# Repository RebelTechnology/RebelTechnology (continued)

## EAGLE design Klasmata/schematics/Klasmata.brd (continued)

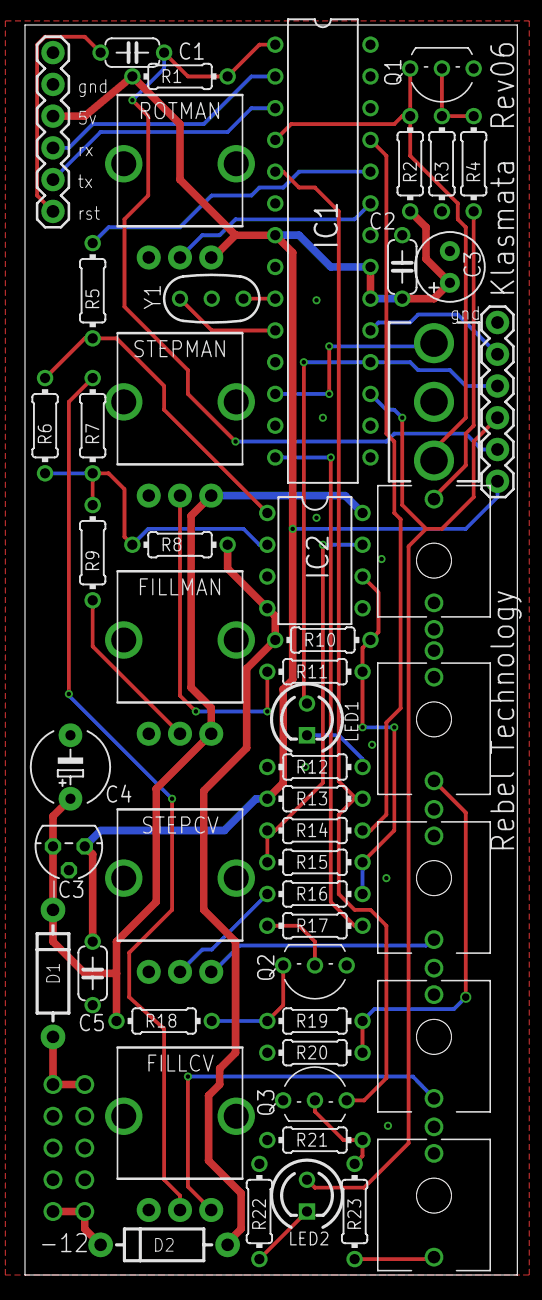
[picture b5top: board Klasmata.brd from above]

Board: 2 copper layers, 39.4 x 100.0 mm, 53 parts (1 on the bottom side), 41 nets.

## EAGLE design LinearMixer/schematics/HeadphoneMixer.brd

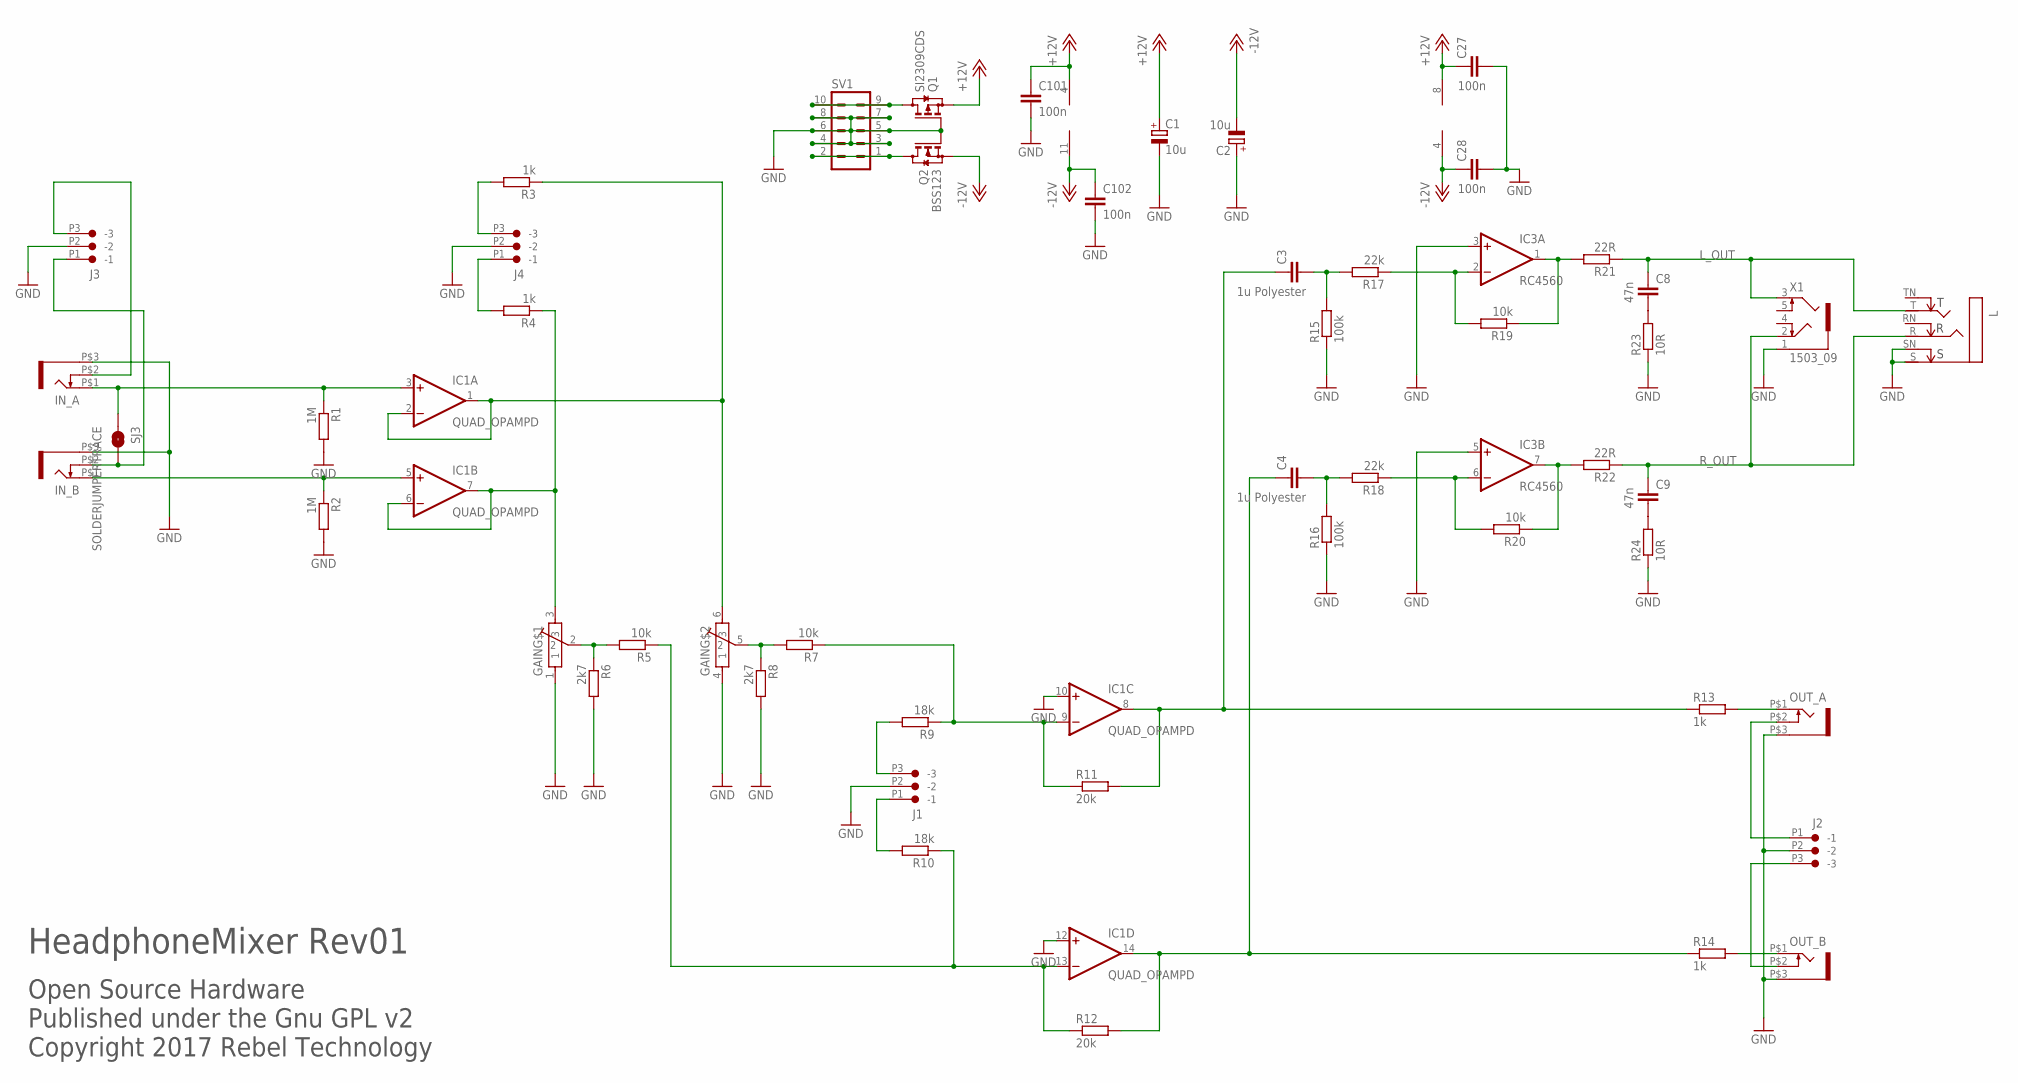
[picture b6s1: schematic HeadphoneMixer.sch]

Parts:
C1, C2: 10u; 153CLV-0505
C3, C4: 1u Polyester; C1210
C8, C9: 47n; C0603
C27, C28, C101, C102: 100n; C0603
GAIN: POT-BOURNS-PTD902
IC1: QUAD_OPAMPD; SO14
IC3: RC4560; SO08
IN_A: JACK-UJ-3502-R; UJ-3502-R
IN_B: JACK-UJ-3502-R; UJ-3502-R
J1, J2, J3, J4: CON-JST_PH_3W
L: NEUTRIK_NMJ6HCD2; NMJ6HCD2
OUT_A: JACK-UJ-3502-R; UJ-3502-R
OUT_B: JACK-UJ-3502-R; UJ-3502-R
Q1: SI2309CDS; SOT23
Q2: BSS123; SOT23
R1, R2: 1M; 0603
R3, R4, R13, R14: 1k; 0603
R5, R7, R19, R20: 10k; 0603
R6, R8: 2k7; 0603
R9, R10: 18k; 0603
R11, R12: 20k; 0603
R15, R16: 100k; 0603
R17, R18: 22k; 0603
R21, R22: 22R; 0603
R23, R24: 10R; 0603
SJ3: SOLDERJUMPERTRACE; SJ_2S-TRACE
SV1: MA05-2
X1: 1503_09

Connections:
+12V: C1.+, C27.1, C101.1, IC1.4 (V+), IC3.8 (V+), Q1.2 (S)
-12V: C2.-, C28.1, C102.1, IC1.11 (V-), IC3.4 (V-), Q2.2 (S)
GND: C1.-, C2.+, C27.2, C28.2, C101.2, C102.2, GAIN.1, GAIN.4 (1), IC1.10 (+IN), IC1.12 (+IN), IC3.3 (+IN), IC3.5 (+IN), IN_A.P$3 (SLEEVE), IN_B.P$3 (SLEEVE), J1.P2 (-2), J2.P2 (-2), J3.P2 (-2), J4.P2 (-2), L.S, L.SN, OUT_A.P$3 (SLEEVE), OUT_B.P$3 (SLEEVE), Q1.1 (G), Q2.1 (G), R1.2, R2.2, R6.2, R8.2, R15.1, R16.1, R23.1, R24.1, SV1.3, SV1.4, SV1.5, SV1.6, SV1.7, SV1.8, X1.1
IN_1: IC1.5 (+IN), IN_B.P$1 (TIP), R2.1
IN_2: IC1.3 (+IN), IN_A.P$1 (TIP), R1.1, SJ3.1
IN_A: J1.P3 (-3), R9.2
IN_A1: IN_A.P$2 (SW), J3.P3 (-3)
IN_A2: J4.P3 (-3), R3.2
IN_B: J1.P1 (-1), R10.2
IN_B1: IN_B.P$2 (SW), J3.P1 (-1), SJ3.2
IN_B2: J4.P1 (-1), R4.2
L_OUT: C8.1, L.T, R21.1, X1.3
unnamed: Q2.3 (D), SV1.1, SV1.2
unnamed: IC3.7 (OUT), R20.1, R22.2
unnamed: IC3.2 (-IN), R17.1, R19.2
unnamed: C4.2, R16.2, R18.2
unnamed: C4.1, IC1.14 (OUT), R12.2, R14.1
unnamed: C3.2, R15.2, R17.2
unnamed: OUT_A.P$1 (TIP), R13.2
unnamed: C3.1, IC1.8 (OUT), R11.2, R13.1
unnamed: GAIN.3, IC1.6 (-IN), IC1.7 (OUT), R4.1
unnamed: C9.2, R24.2
unnamed: GAIN.6 (3), IC1.1 (OUT), IC1.2 (-IN), R3.1
unnamed: Q1.3 (D), SV1.9, SV1.10
unnamed: OUT_B.P$1 (TIP), R14.2
unnamed: IC3.6 (-IN), R18.1, R20.2
unnamed: IC3.1 (OUT), R19.1, R21.2
unnamed: C8.2, R23.2
unnamed: GAIN.2, R5.2, R6.1
unnamed: IC1.13 (-IN), R5.1, R10.1, R12.1
unnamed: IC1.9 (-IN), R7.1, R9.1, R11.1
unnamed: GAIN.5 (2), R7.2, R8.1
OUT_SW_A: J2.P1 (-1), OUT_A.P$2 (SW)
OUT_SW_B: J2.P3 (-3), OUT_B.P$2 (SW)
R_OUT: C9.1, L.R, R22.1, X1.2

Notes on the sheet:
Open Source Hardware Published under the Gnu GPL v2 Copyright 2017 Rebel Technology
HeadphoneMixer Rev01

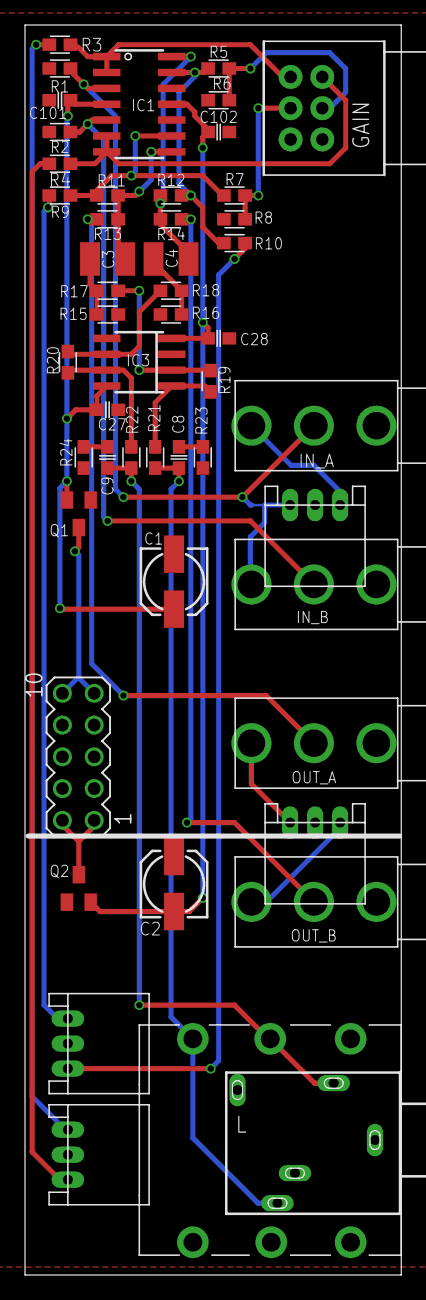
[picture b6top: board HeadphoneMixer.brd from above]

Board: 2 copper layers, 30.1 x 100.0 mm, 51 parts (1 on the bottom side), 35 nets.
